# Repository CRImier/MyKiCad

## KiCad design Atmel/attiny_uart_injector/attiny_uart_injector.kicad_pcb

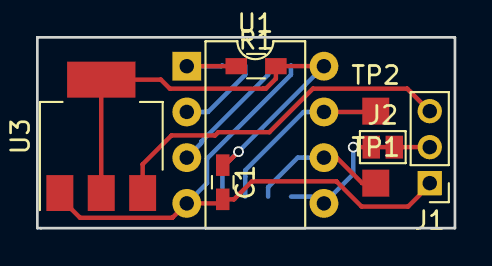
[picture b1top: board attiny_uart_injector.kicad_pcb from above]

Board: 2 copper layers, 23.2 x 10.6 mm, 9 parts (1 on the bottom side), 9 nets.

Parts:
C1: C_Small; C_0603_HandSoldering
J1: CONN_01X03; Pin_Header_Straight_1x03_Pitch2.00mm
J2: TEST_2P; GS2
R1: R_Small; R_0603_HandSoldering
TP1, TP2: TEST; Measurement_Point_Square-SMD-Pad_Small
U1: ATTINY85-20PU; DIP-8_W7.62mm
U2: ATTINY85-20PU; SOIJ-8_5.3x5.3mm_Pitch1.27mm
U3: LM1117-3.3; SOT-223

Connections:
+3V3: C1.1, R1.2, U1.8, U2.8, U3.2, U3.4
GND: C1.2, J1.1, U1.4, U2.4, U3.1
unnamed: J1.2, J2.1, J2.2, U1.5, U2.5
unnamed: R1.1, U1.1, U2.1
unnamed: TP1.1, U1.6, U2.6
unnamed: TP2.1, U1.7, U2.7
unnamed: U1.2, U2.2
unnamed: U1.3, U2.3
VCC: J1.3, U3.3

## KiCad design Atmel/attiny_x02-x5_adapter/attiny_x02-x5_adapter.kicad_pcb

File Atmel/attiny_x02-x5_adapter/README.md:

# ATTiny x02 - x5 adapter

This is an adapter to fit an ATTinyx02 (i.e. ATTiny402) instead of ATTinyx5 (i.e. ATTiny85).
It solders as an LGA board. It might also work with ATTinyx12 (i.e. ATTiny412), but I haven't checked

It won't support ISP, since, it seems, ATTinyx02 wants UPDI. Make sure your RESET isn't hard-pulled to VCC,
I guess.

If you want to use this for your own purposes, make sure that the pinout mapping suits you.
If it doesn't, change the mapping and reroute the board.

If you're ordering many of these, using DirtyPCBs for ordering and ThisIsNotRocketScience
GerberPanelizer is the easiest and the most cost-efficient option, in my experience.

You'll also certainly need to change the code for the new CPU, good luck with that.

This board is untested and there's no guarantees of fitness.

- PCB size: 9,5*6mm
- Layer count: 2

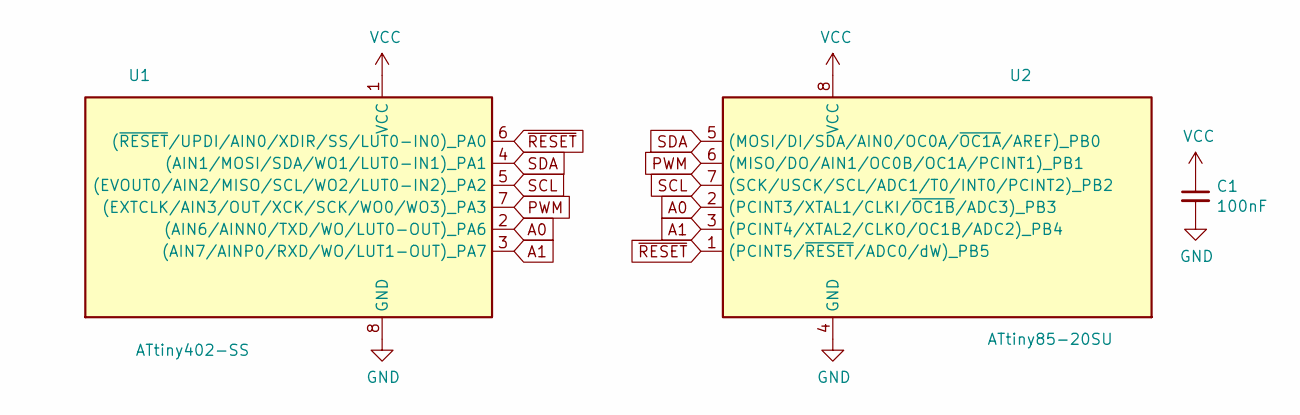
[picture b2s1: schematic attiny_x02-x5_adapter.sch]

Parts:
C1: 100nF; C_0805_2012Metric
U1: ATtiny402-SS; SOIC-8_3.9x4.9mm_P1.27mm
U2: ATtiny85-20SU; SOIJ-8_5.3x5.3mm_P1.27mm_Flipped

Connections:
A0: U1.2 ((AIN6/AINN0/TXD/WO/LUT0-OUT)_PA6), U2.2 ((PCINT3/XTAL1/CLKI/~OC1B~/ADC3)_PB3)
A1: U1.3 ((AIN7/AINP0/RXD/WO/LUT1-OUT)_PA7), U2.3 ((PCINT4/XTAL2/CLKO/OC1B/ADC2)_PB4)
GND: C1.2, U1.8 (GND), U2.4 (GND)
PWM: U1.7 ((EXTCLK/AIN3/OUT/XCK/SCK/WO0/WO3)_PA3), U2.6 ((MISO/DO/AIN1/OC0B/OC1A/PCINT1)_PB1)
SCL: U1.5 ((EVOUT0/AIN2/MISO/SCL/WO2/LUT0-IN2)_PA2), U2.7 ((SCK/USCK/SCL/ADC1/T0/INT0/PCINT2)_PB2)
SDA: U1.4 ((AIN1/MOSI/SDA/WO1/LUT0-IN1)_PA1), U2.5 ((MOSI/DI/SDA/AIN0/OC0A/~OC1A~/AREF)_PB0)
VCC: C1.1, U1.1 (VCC), U2.8 (VCC)
~RESET: U1.6 ((~RESET~/UPDI/AIN0/XDIR/SS/LUT0-IN0)_PA0), U2.1 ((PCINT5/~RESET~/ADC0/dW)_PB5)

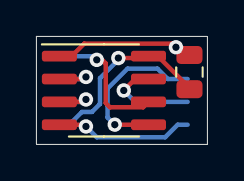
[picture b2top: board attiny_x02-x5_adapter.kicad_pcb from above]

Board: 2 copper layers, 9.5 x 6.0 mm, 3 parts (0 on the bottom side), 8 nets.

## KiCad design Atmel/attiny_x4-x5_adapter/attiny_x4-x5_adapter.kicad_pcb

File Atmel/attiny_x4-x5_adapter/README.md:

# ATTiny x4 - x5 adapter

This is an adapter to fit an ATTinyx4 (i.e. ATTiny84) instead of ATTinyx5 (i.e. ATTiny85).
It solders as an LGA board.

The current mapping seems to preserve the ISP pin mapping on the same pins.
I'm not 100% certain it will work, but I tried!

If you want to use this for your own purposes, make sure that the pinout mapping suits you.
If it doesn't, change the mapping and reroute the board.

If you're ordering many of these, using DirtyPCBs for ordering and ThisIsNotRocketScience
GerberPanelizer is the easiest and the most cost-efficient option, in my experience.

You'll also certainly need to change the code for the new CPU, good luck with that.

This board is untested and there's no guarantees of fitness.

- PCB size: 9,5*6mm
- Layer count: 2

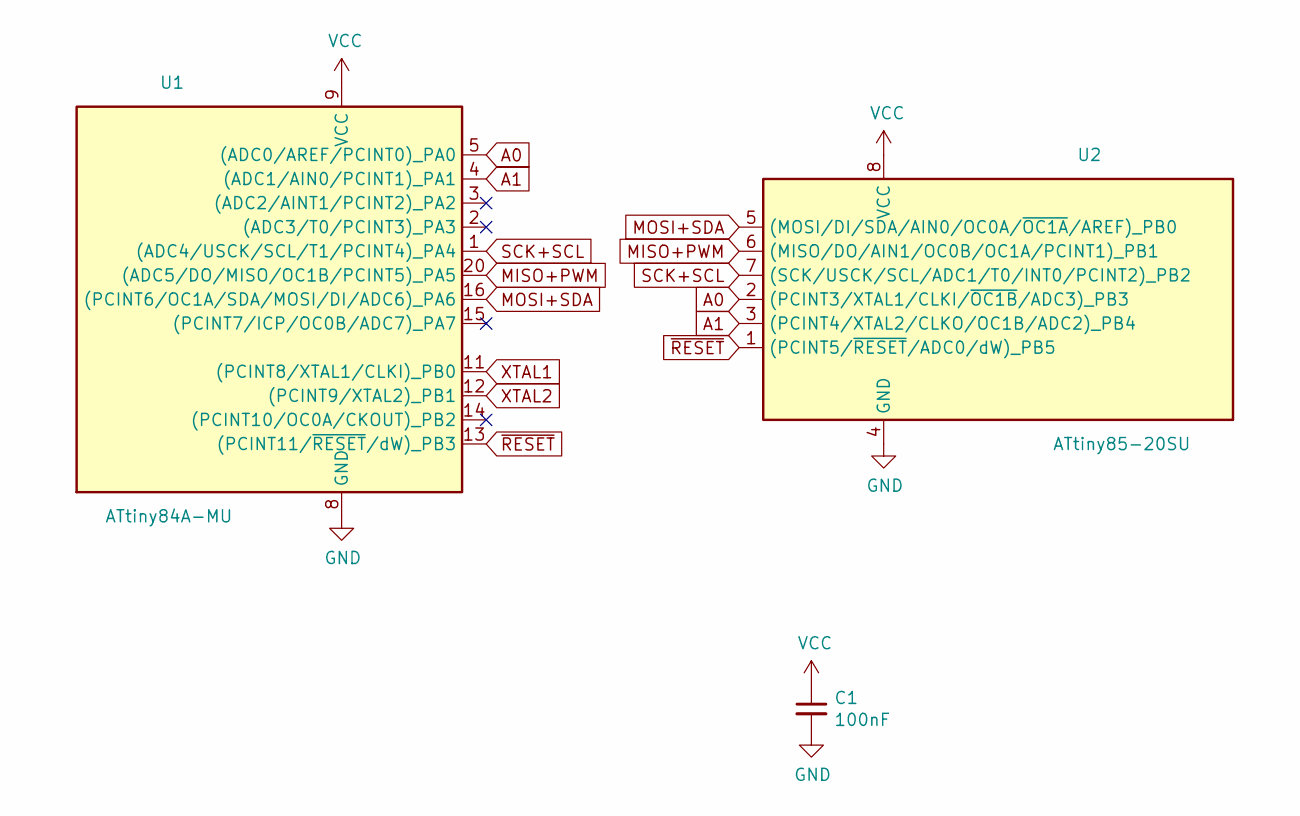
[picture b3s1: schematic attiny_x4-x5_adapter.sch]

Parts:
C1: 100nF; C_0805_2012Metric
U1: ATtiny84A-MU; QFN-20-1EP_4x4mm_P0.5mm_EP2.6x2.6mm
U2: ATtiny85-20SU; SOIJ-8_5.3x5.3mm_P1.27mm_Flipped

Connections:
A0: U1.5 ((ADC0/AREF/PCINT0)_PA0), U2.2 ((PCINT3/XTAL1/CLKI/~OC1B~/ADC3)_PB3)
A1: U1.4 ((ADC1/AIN0/PCINT1)_PA1), U2.3 ((PCINT4/XTAL2/CLKO/OC1B/ADC2)_PB4)
GND: C1.2, U1.8 (GND), U1.21 (GND), U2.4 (GND)
MISO+PWM: U1.20 ((ADC5/DO/MISO/OC1B/PCINT5)_PA5), U2.6 ((MISO/DO/AIN1/OC0B/OC1A/PCINT1)_PB1)
MOSI+SDA: U1.16 ((PCINT6/OC1A/SDA/MOSI/DI/ADC6)_PA6), U2.5 ((MOSI/DI/SDA/AIN0/OC0A/~OC1A~/AREF)_PB0)
SCK+SCL: U1.1 ((ADC4/USCK/SCL/T1/PCINT4)_PA4), U2.7 ((SCK/USCK/SCL/ADC1/T0/INT0/PCINT2)_PB2)
VCC: C1.1, U1.9 (VCC), U2.8 (VCC)
XTAL1: U1.11 ((PCINT8/XTAL1/CLKI)_PB0)
XTAL2: U1.12 ((PCINT9/XTAL2)_PB1)
~RESET: U1.13 ((PCINT11/~RESET~/dW)_PB3), U2.1 ((PCINT5/~RESET~/ADC0/dW)_PB5)

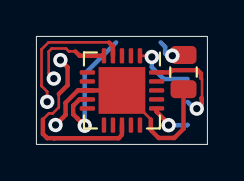
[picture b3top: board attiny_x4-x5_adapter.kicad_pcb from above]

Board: 2 copper layers, 9.5 x 6.0 mm, 3 parts (0 on the bottom side), 8 nets.

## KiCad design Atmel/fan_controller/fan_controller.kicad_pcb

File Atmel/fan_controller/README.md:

# Universal ATTiny fan controller

This is an ATTiny-driven fan controller board for driving 5V or 12V fans, 3-pin and 4-pin ones.
It allows you to control the fan speed with a potentiometer or through I2C -
assuming your firmware supports this, I haven't written any firmware for this board yet.

There are two solder jumpers on the bottom of the board - one allows you to drive a 4-pin fan
by bypassing the FET control of the fan's VCC line, and the second one allows for 5V fans
(with 5V VCC). The 5V VCC can be taken from the I2C header, but two through-hole pads have
to be shorted for that to be possible - they're intended for a through-hole side switch.
This is so that you don't accidentally power this device from a low-power I2C header.

There's a potentiometer header on this board, you could also use a thermistor in place of
a potentiometer if you'd like. There's also a tachometer input, shunted through a 5V zener diode
to not overvolt the ATTiny input in case of a 12V fan.

There's an ISP header for reprogramming the ATTiny, the ISP header has to be plugged in
from the underside of the board. There's also a RPi-style I2C header,
but this board can't be plugged directly into a RPi, since it's a 5V I2C connection
and it would destroy the Pi's I2C input when plugged directly, you need a level shifter board for that.
There are no I2C pullups on this board, however, so that might be possible if you don't short
the I2C 5V jumper pads.

Fan and power input signal names are silkscreened on the board, top and bottom layers. I2C and ISP signals
are unmarked.

- PCB size: 35*14mm
- Layer count: 2

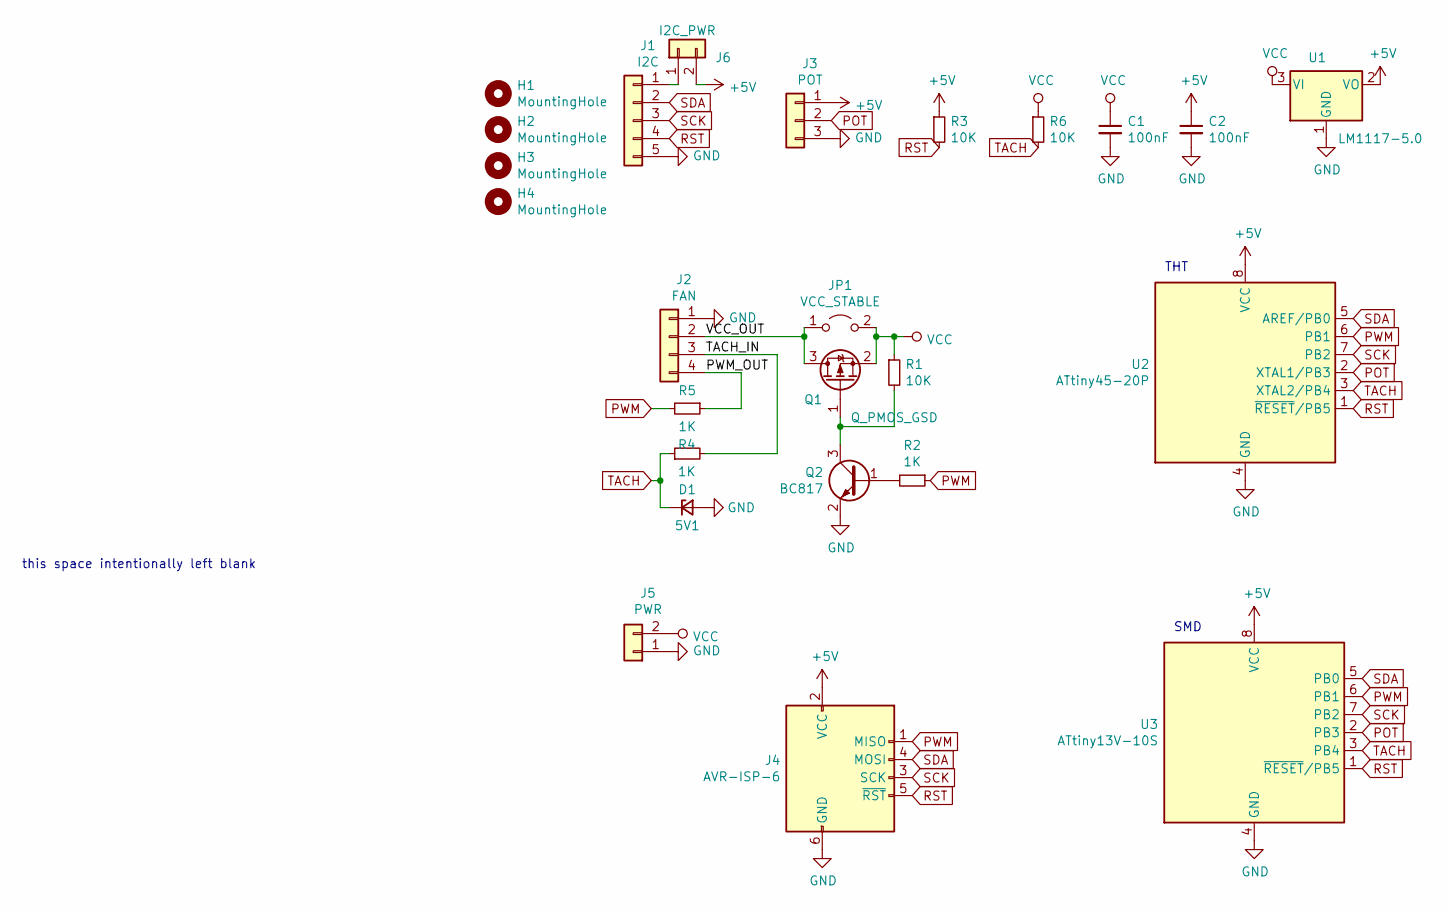
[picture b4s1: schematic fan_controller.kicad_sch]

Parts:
C1, C2: 100nF; C_0805_2012Metric
D1: 5V1; D_SOD-123
H1, H2, H3, H4: MountingHole; MountingHole_2.1mm
J1: I2C; PinHeader_1x05_P2.54mm_Vertical
J2: FAN; PinHeader_1x04_P2.54mm_Vertical
J3: POT; PinHeader_1x03_P2.54mm_Vertical
J4: AVR-ISP-6; PinHeader_2x03_P2.54mm_Vertical
J5: PWR; PinHeader_1x02_P2.54mm_Vertical
J6: I2C_PWR; PinHeader_1x02_P2.54mm_Vertical
JP1: VCC_STABLE; SolderJumper-2_P1.3mm_Open_Pad1.0x1.5mm
Q1: Q_PMOS_GSD; SOT-23
Q2: BC817; SOT-23
R1, R3, R6: 10K; R_0805_2012Metric
R2, R4, R5: 1K; R_0805_2012Metric
U1: LM1117-5.0; SOT-223-3_TabPin2
U2: ATtiny45-20P; DIP-8_W7.62mm
U3: ATtiny13V-10S; SOIC-8W_5.3x5.3mm_P1.27mm

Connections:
+5V: C2.1, J3.1, J4.2 (VCC), J6.2, R3.1, U1.2 (VO), U2.8 (VCC), U3.8 (VCC)
/PWM_OUT: J2.4, R5.1
/TACH_IN: J2.3, R4.2
/VCC_OUT: J2.2, JP1.1 (A), Q1.3 (D)
GND: C1.2, C2.2, D1.2 (A), J1.5, J2.1, J3.3, J4.6 (GND), J5.1, Q2.2 (E), U1.1 (GND), U2.4 (GND), U3.4 (GND)
unnamed: J1.1, J6.1
unnamed: Q1.1 (G), Q2.3 (C), R1.2
unnamed: Q2.1 (B), R2.2
POT: J3.2, U2.2 (XTAL1/PB3), U3.2 (PB3)
PWM: J4.1 (MISO), R2.1, R5.2, U2.6 (PB1), U3.6 (PB1)
RST: J1.4, J4.5 (~RST), R3.2, U2.1 (~RESET/PB5), U3.1 (~RESET/PB5)
SCK: J1.3, J4.3 (SCK), U2.7 (PB2), U3.7 (PB2)
SDA: J1.2, J4.4 (MOSI), U2.5 (AREF/PB0), U3.5 (PB0)
TACH: D1.1 (K), R4.1, R6.2, U2.3 (XTAL2/PB4), U3.3 (PB4)
VCC: C1.1, J5.2, JP1.2 (B), Q1.2 (S), R1.1, R6.1, U1.3 (VI)

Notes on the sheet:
THT
SMD
this space intentionally left blank

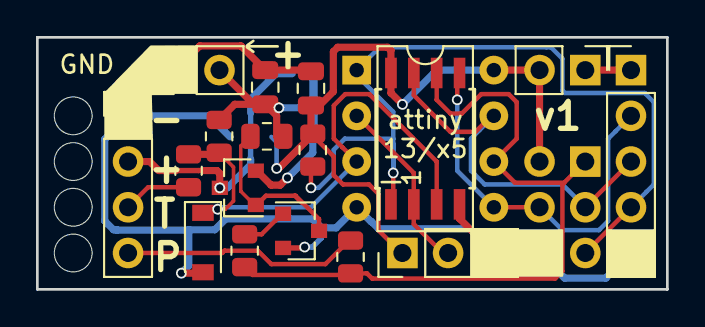
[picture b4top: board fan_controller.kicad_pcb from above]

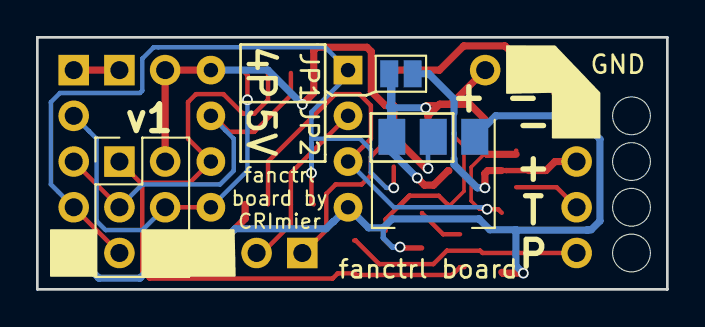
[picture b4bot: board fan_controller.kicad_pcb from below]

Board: 2 copper layers, 35.0 x 14.0 mm, 25 parts (3 on the bottom side), 15 nets.

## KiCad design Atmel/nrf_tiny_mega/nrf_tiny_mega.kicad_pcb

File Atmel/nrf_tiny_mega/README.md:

https://hackaday.io/project/166648-saferspace

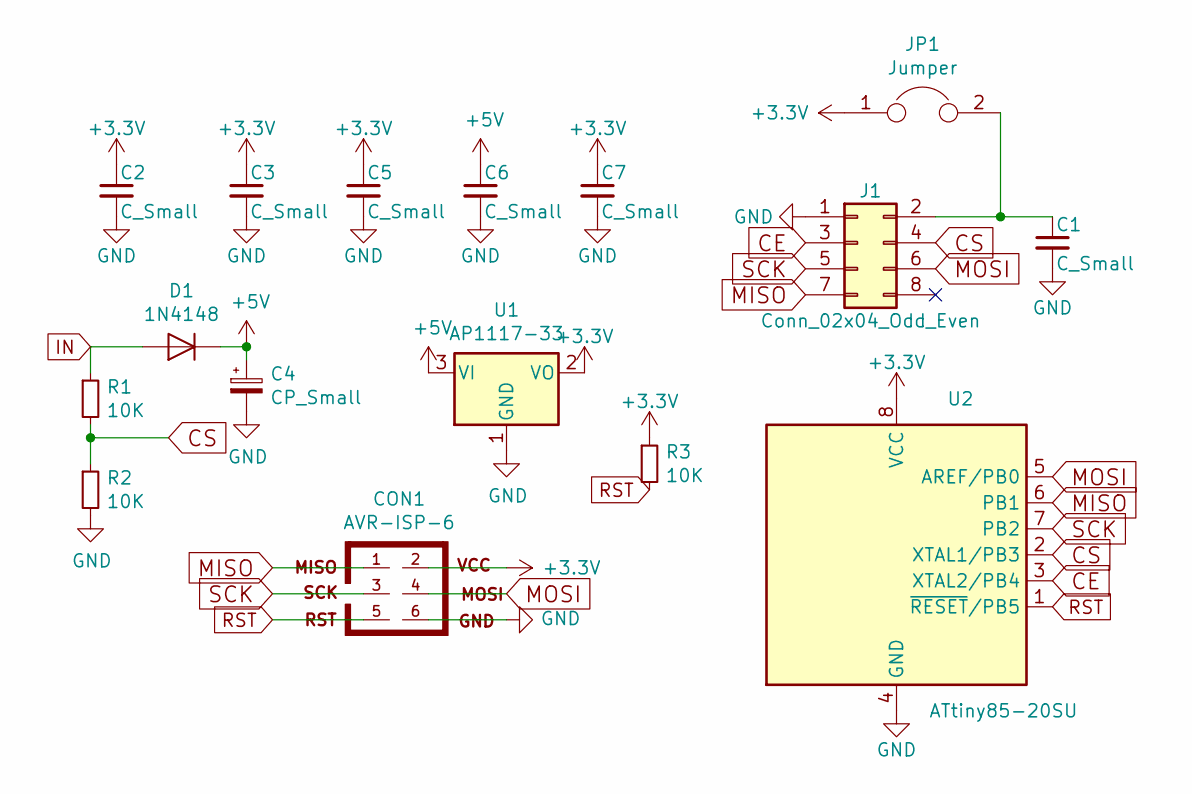
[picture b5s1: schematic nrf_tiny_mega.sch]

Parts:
C1, C2, C3, C5, C6, C7: C_Small; C_0805_2012Metric_Pad1.15x1.40mm_HandSolder
C4: CP_Small; CP_Radial_D10.0mm_P2.50mm_P5.00mm
CON1: AVR-ISP-6; PinHeader_2x03_P2.54mm_Vertical
D1: 1N4148; D_DO-35_SOD27_P7.62mm_Horizontal
J1: Conn_02x04_Odd_Even; PinHeader_2x04_P2.54mm_Vertical
JP1: Jumper; SolderJumper-2_P1.3mm_Open_Pad1.0x1.5mm
R1, R2, R3: 10K; R_0805_2012Metric_Pad1.15x1.40mm_HandSolder
U1: AP1117-33; SOT-223-3_TabPin2
U2: ATtiny85-20SU; SOIJ-8_5.3x5.3mm_P1.27mm

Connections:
+3V3: C2.1, C3.1, C5.1, C7.1, CON1.2, JP1.1, R3.1, U1.2 (VO), U2.8 (VCC)
+5V: C4.1, C6.1, D1.1 (K), U1.3 (VI)
CE: J1.3, U2.3 (XTAL2/PB4)
CS: J1.4, R1.2, R2.1, U2.2 (XTAL1/PB3)
GND: C1.2, C2.2, C3.2, C4.2, C5.2, C6.2, C7.2, CON1.6, J1.1, R2.2, U1.1 (GND), U2.4 (GND)
IN: D1.2 (A), R1.1
MISO: CON1.1, J1.7, U2.6 (PB1)
MOSI: CON1.4, J1.6, U2.5 (AREF/PB0)
unnamed: C1.1, J1.2, JP1.2
RST: CON1.5, R3.2, U2.1 (~RESET~/PB5)
SCK: CON1.3, J1.5, U2.7 (PB2)

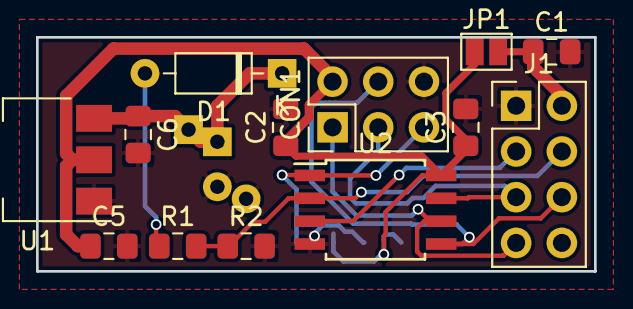
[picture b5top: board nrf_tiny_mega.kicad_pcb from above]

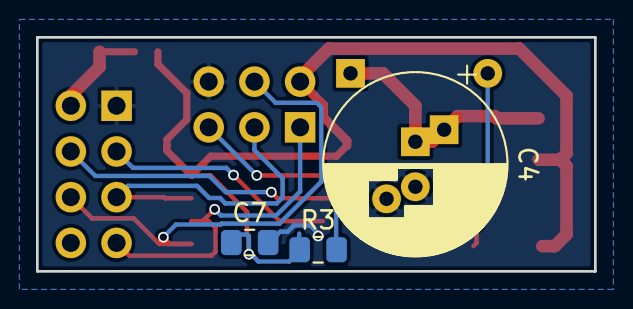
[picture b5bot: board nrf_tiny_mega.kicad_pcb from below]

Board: 2 copper layers, 31.0 x 13.0 mm, 16 parts (3 on the bottom side), 11 nets.

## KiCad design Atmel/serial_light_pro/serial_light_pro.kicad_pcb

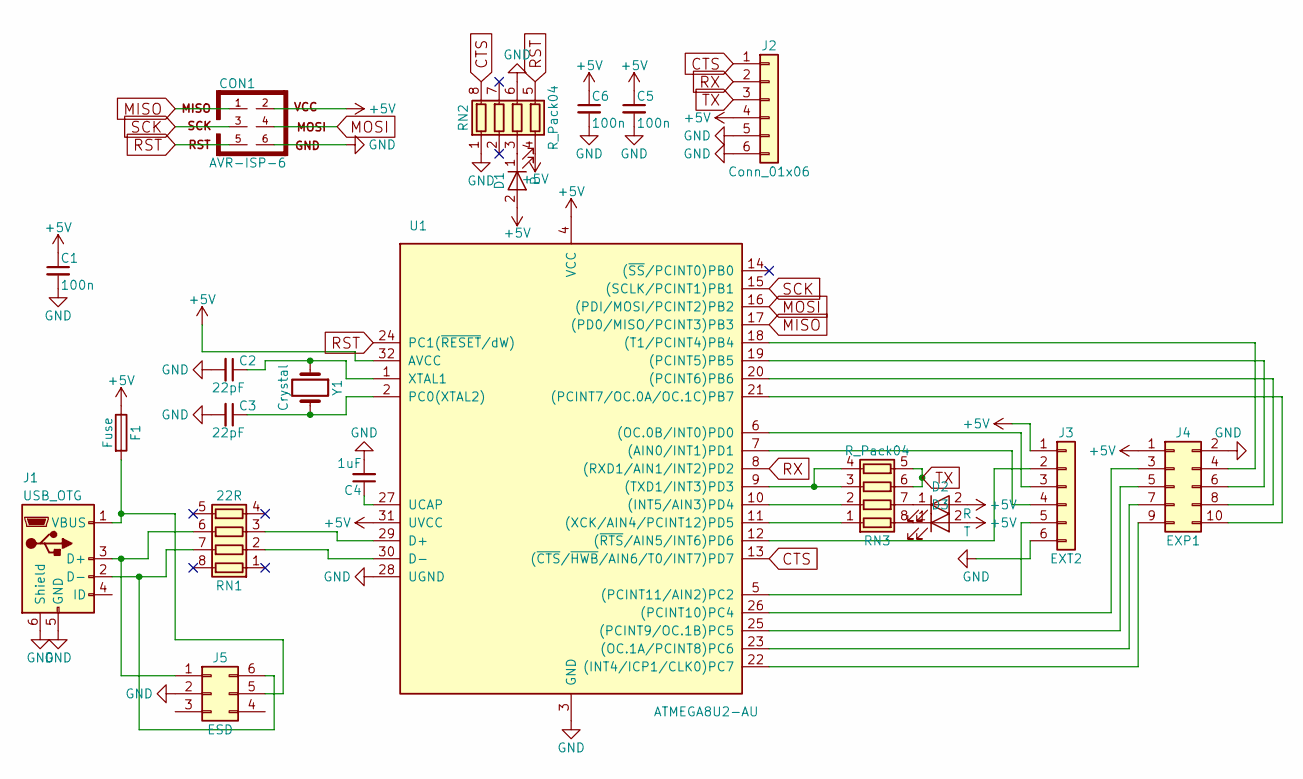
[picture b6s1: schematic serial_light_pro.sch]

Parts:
C1, C5, C6: 100n; C_0603_HandSoldering
C2, C3: 22pF; C_0603_HandSoldering
C4: 1uF; C_0805_HandSoldering
CON1: AVR-ISP-6; Pin_Header_Straight_2x03_Pitch2.54mm
D1: P; LED_0805
D2: R; LED_0805
D3: T; LED_0805
F1: Fuse; Fuse_SMD1206_Wave
J1: USB_OTG; USB_Micro-B
J2: Conn_01x06; Socket_Strip_Angled_1x06_Pitch2.54mm
J3: EXT2
J4: EXP1; Pin_Header_Straight_2x05_Pitch2.00mm_SMD
J5: ESD; SOT-23-6
RN1: 22R; R_Array_Convex_4x0603
RN2, RN3: R_Pack04; R_Array_Concave_4x0402
U1: ATMEGA8U2-AU; QFN-32-1EP_5x5mm_Pitch0.5mm
Y1: Crystal; Crystal_HC49-U_Vertical

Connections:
+5V: C1.1, C5.1, C6.1, CON1.2, D1.2 (A), D2.2 (A), D3.2 (A), F1.1, J2.4, J3.1, J4.1, RN2.4 (R4.1), U1.4 (VCC), U1.31 (UVCC), U1.32 (AVCC)
CTS: J2.1, RN2.8 (R1.2), U1.13 ((~CTS~/~HWB~/AIN6/T0/INT7)PD7)
GND: C1.2, C2.2, C3.2, C4.2, C5.2, C6.2, CON1.6, J1.5 (GND), J1.6 (Shield), J2.5, J2.6, J3.6, J4.2, J5.2, RN2.1 (R1.1), RN2.6 (R3.2), U1.3 (GND), U1.28 (UGND), U1.33
MISO: CON1.1, U1.17 ((PD0/MISO/PCINT3)PB3)
MOSI: CON1.4, U1.16 ((PDI/MOSI/PCINT2)PB2)
unnamed: C2.1, U1.1 (XTAL1), Y1.1
unnamed: C3.1, U1.2 (PC0(XTAL2)), Y1.2
unnamed: C4.1, U1.27 (UCAP)
unnamed: D1.1 (K), RN2.3 (R3.1)
unnamed: D2.1 (K), RN3.7 (R2.2)
unnamed: D3.1 (K), RN3.8 (R1.2)
unnamed: F1.2, J1.1 (VBUS), J5.5
unnamed: J1.2 (D-), J5.6, RN1.7 (R2.2)
unnamed: J1.3 (D+), J5.1, RN1.6 (R3.2)
unnamed: J3.2, U1.12 ((~RTS~/AIN5/INT6)PD6)
unnamed: J3.3, U1.6 ((OC.0B/INT0)PD0)
unnamed: J3.4, U1.7 ((AIN0/INT1)PD1)
unnamed: J3.5, U1.5 ((PCINT11/AIN2)PC2)
unnamed: J4.3, U1.26 ((PCINT10)PC4)
unnamed: J4.4, U1.18 ((T1/PCINT4)PB4)
unnamed: J4.5, U1.25 ((PCINT9/OC.1B)PC5)
unnamed: J4.6, U1.19 ((PCINT5)PB5)
unnamed: J4.7, U1.23 ((OC.1A/PCINT8)PC6)
unnamed: J4.8, U1.20 ((PCINT6)PB6)
unnamed: J4.9, U1.22 ((INT4/ICP1/CLK0)PC7)
unnamed: J4.10, U1.21 ((PCINT7/OC.0A/OC.1C)PB7)
unnamed: RN1.2 (R2.1), U1.30 (D-)
unnamed: RN1.3 (R3.1), U1.29 (D+)
unnamed: RN3.1 (R1.1), U1.11 ((XCK/AIN4/PCINT12)PD5)
unnamed: RN3.2 (R2.1), U1.10 ((INT5/AIN3)PD4)
unnamed: RN3.3 (R3.1), RN3.4 (R4.1), U1.9 ((TXD1/INT3)PD3)
RST: CON1.5, RN2.5 (R4.2), U1.24 (PC1(~RESET~/dW))
RX: J2.2, U1.8 ((RXD1/AIN1/INT2)PD2)
SCK: CON1.3, U1.15 ((SCLK/PCINT1)PB1)
TX: J2.3, RN3.5 (R4.2), RN3.6 (R3.2)

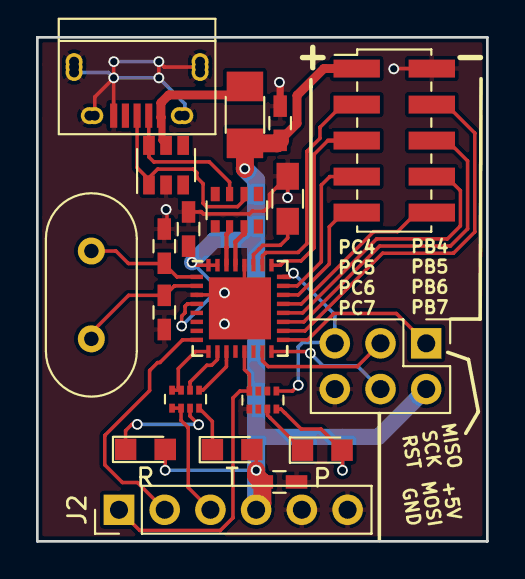
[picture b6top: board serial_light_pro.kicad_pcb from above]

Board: 2 copper layers, 25.0 x 28.0 mm, 20 parts (0 on the bottom side), 31 nets.

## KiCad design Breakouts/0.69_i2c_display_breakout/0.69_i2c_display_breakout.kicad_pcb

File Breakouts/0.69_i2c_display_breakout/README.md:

# 0.69 I2C display breakout

This is a breakout PCB for 0.69 "SSD1306" 96x16 displays
commonly used on TS100/TS80/Pinecil soldering irons.
It uses the Raspberry Pi I2C pinout and poweers from 3.3V.

Signal names are silkscreened on the board's bottom layers.
This board is untested and there's no guarantees of fitness.

- PCB size: 16*15mm
- Layer count: 2

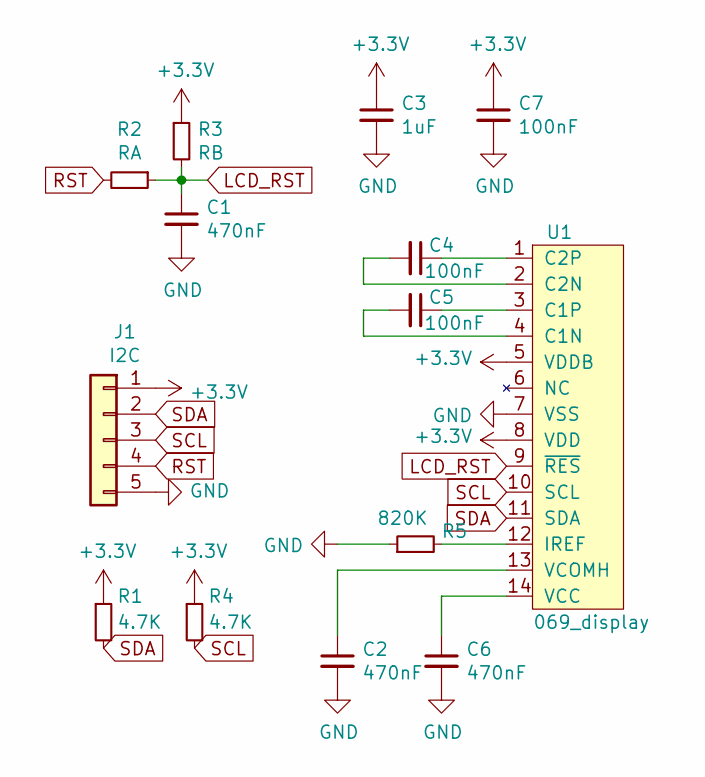
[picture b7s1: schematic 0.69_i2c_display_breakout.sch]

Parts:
C1, C2, C6: 470nF; C_0805_2012Metric
C3: 1uF; C_0805_2012Metric
C4, C5, C7: 100nF; C_0805_2012Metric
J1: I2C; PinHeader_1x05_P2.54mm_Vertical
R1, R4: 4.7K; R_0805_2012Metric
R2: RA; R_0805_2012Metric
R3: RB; R_0805_2012Metric
R5: 820K; R_0805_2012Metric
U1: 069_display

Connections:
+3V3: C3.1, C7.1, J1.1, R1.1, R3.1, R4.1, U1.5 (VDDB), U1.8 (VDD)
GND: C1.2, C2.2, C3.2, C6.2, C7.2, J1.5, R5.1, U1.7 (VSS)
LCD_RST: C1.1, R2.1, R3.2, U1.9 (~RES)
unnamed: C2.1, U1.13 (VCOMH)
unnamed: C4.1, U1.1 (C2P)
unnamed: C4.2, U1.2 (C2N)
unnamed: C5.1, U1.3 (C1P)
unnamed: C5.2, U1.4 (C1N)
unnamed: C6.1, U1.14 (VCC)
unnamed: R5.2, U1.12 (IREF)
RST: J1.4, R2.2
SCL: J1.3, R4.2, U1.10 (SCL)
SDA: J1.2, R1.2, U1.11 (SDA)

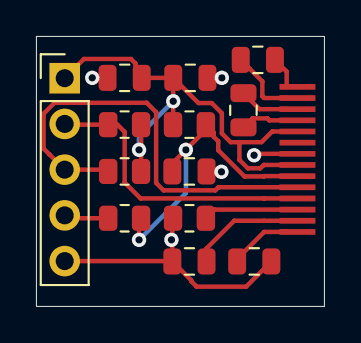
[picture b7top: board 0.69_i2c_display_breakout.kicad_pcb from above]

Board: 2 copper layers, 16.0 x 15.0 mm, 14 parts (0 on the bottom side), 13 nets.

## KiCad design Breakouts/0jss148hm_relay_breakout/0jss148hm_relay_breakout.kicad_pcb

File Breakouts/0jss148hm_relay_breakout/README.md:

# 0J-SS-148HM relay breakout

Breakout for SPST 48V relays - our hackerspace has, like, 50 of these.
It's optoisolated, control signal GND can be completely separate from the relay GND.

Signal names are silkscreened on the board, top and bottom layers.
This repository also includes files for manufacturing a 2x9 panel.

- PCB size: 40*11mm
- Layer count: 2

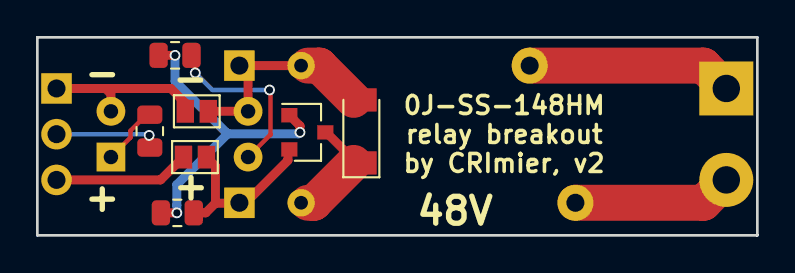
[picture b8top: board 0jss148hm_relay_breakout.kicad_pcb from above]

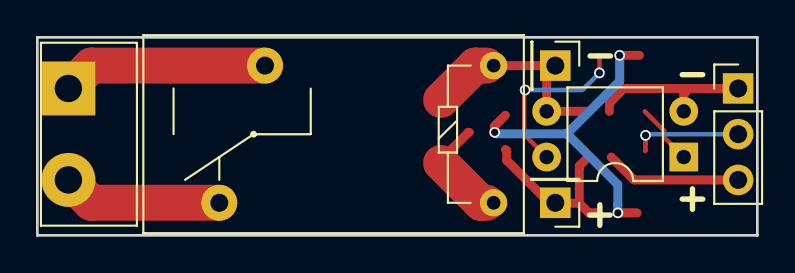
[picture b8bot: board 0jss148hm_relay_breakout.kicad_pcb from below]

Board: 2 copper layers, 40.0 x 11.0 mm, 13 parts (6 on the bottom side), 11 nets.

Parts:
D1: D_Small; D_MiniMELF
J1: Conn_01x03; Pin_Header_Straight_1x03_Pitch2.54mm
J2, J4: Conn_01x01; Pin_Header_Straight_1x01_Pitch2.54mm
J5: Conn_01x02; TerminalBlock_bornier-2_P5.08mm
JP1, JP2: Jumper; GS2
K1: G5Q-1A; Relay_SPDT_OMRON-G5Q
Q1: Q_PNP_BEC; SOT-23
R1: 1K; R_0805_2012Metric
R2: 50K; R_0805_2012Metric
R3: 10K; R_0805_2012Metric
U1: PC817; DIP-4_W7.62mm

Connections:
GND: J1.1, JP2.1, U1.2
unnamed: D1.1, K1.5, Q1.3
unnamed: D1.2, J2.1, JP2.2, K1.1, U1.3
unnamed: J1.2, R1.2
unnamed: J4.1, JP1.2, Q1.2, R2.2
unnamed: J5.1, K1.2
unnamed: J5.2, K1.3
unnamed: Q1.1, R2.1, R3.1
unnamed: R1.1, U1.1
unnamed: R3.2, U1.4
VCC: J1.3, JP1.1
